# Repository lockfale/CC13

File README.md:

# CC13:
CarolinaCon13 Badge Jank

## Files:
- CC13 Badge.pdf - Detailed badge assembly guide
- ino files

## If you need to setup an Arduino build environment:

Download the latest Arduino archive from https://www.arduino.cc/en/Main/Software

Uncompress archive: xz --decompress arduino-1.8.2-linux64.tar.xz

As root untar in /usr/local and create symlink:
```
    # cd /usr/local
    # tar xvf ~/Downloads/arduino-1.8.2-linux64.tar
    # ln -s arduino-1.8.2/ arduino
```

As regular user, download badge code into home directory (--recursive will pull down dependency projects):
```
    cd
    git clone --recursive https://github.com/lockfale/CC13.git
```

## LED Patterns

To add an LED pattern:
  # In `badge/led.cpp`:
    ## Add a `const byte` array to with its own name and each sequential animation state of your desired LED pattern in binary format matching the number of LEDs in each entry.
    ## Add a branch to the `changePattern` function.
    ## Add a function for it at the bottom.
  # In `badge/led.h`:
    ## Add a function for it at the bottom.
  # In `badge/setup.cpp`:
    ## Add a submenu command for it.

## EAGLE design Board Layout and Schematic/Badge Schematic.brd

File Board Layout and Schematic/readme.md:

this is an older beta design, may not work properly but should be close.

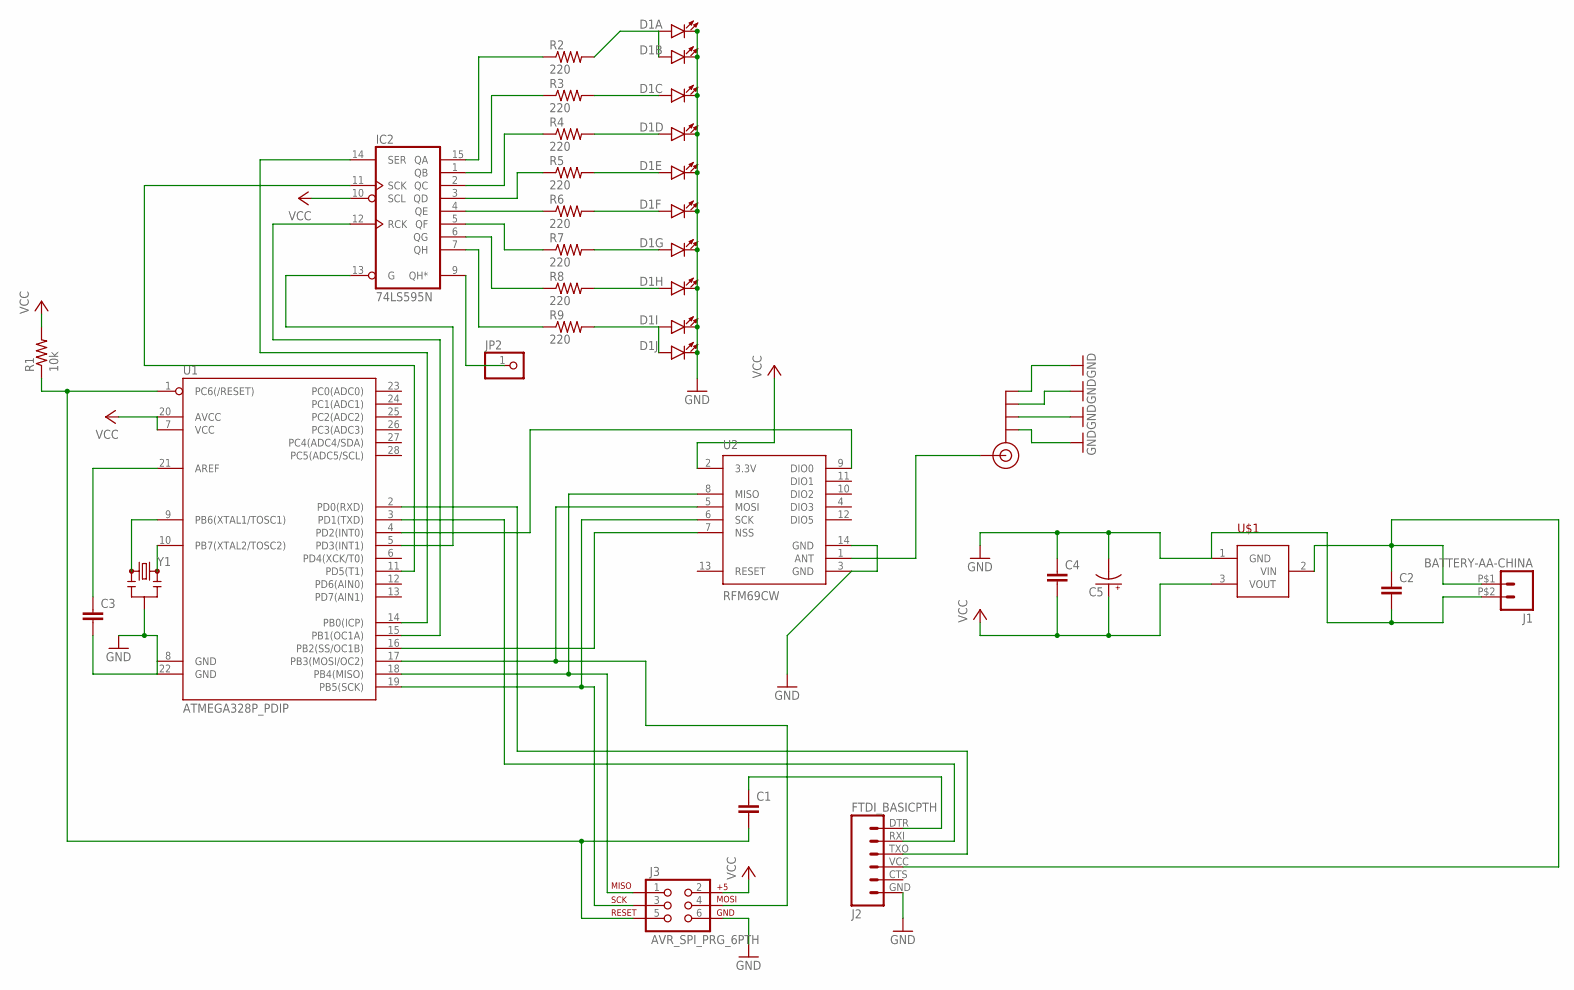
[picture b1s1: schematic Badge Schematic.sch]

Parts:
C1, C2, C3, C4: 0.1UF-50V-20%(PTH)KIT-EZ; CAP-PTH-SMALL-KIT
C5: 10UF-25V-20%(PTH)KIT; CPOL-RADIAL-10UF-25V-KIT
D1: LED_BARGRAPH_10; LED_BARGAPH_10
IC2: 74LS595N; DIL16
J1: BATTERY-AA-CHINA; BATTERY-AA-CHINA-PACKAGE
J2: FTDI_BASICPTH; FTDI_BASIC
J3: AVR_SPI_PRG_6PTH; 2X3
J$1: SMA_EDGE; SMA-EDGE
JP2: PINHD-1X1; 1X01
R1: 10k; AXIAL-0.3
R2, R3, R4, R5, R6, R7, R8, R9: 220; AXIAL-0.3EZ
U1: ATMEGA328P_PDIP; DIL28-3
U2: RFM69CW; RFM69CW-XXXS2
U$1: MCP1702-33TO92; TO-92
Y1: RESONATORPTH; RESONATOR-PTH

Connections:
GND: C2.2, C3.2, C4.1, C5.2 (-), D1.11 (C), D1.12 (C), D1.13 (C), D1.14 (C), D1.15 (C), D1.16 (C), D1.17 (C), D1.18 (C), D1.19 (C), D1.20 (C), IC2.8 (GND), J1.P$2 (2), J2.GND (6), J3.6, J$1.GND@0 (GND), J$1.GND@1 (GND), J$1.GND@2 (GND), J$1.GND@3 (GND), U1.8 (GND), U1.22 (GND), U2.3 (GND), U2.14 (GND), U$1.1 (GND), Y1.2
unnamed: J$1.SIG (SIGNAL), U2.1 (ANT)
unnamed: J3.4, U1.17 (PB3(MOSI/OC2)), U2.5 (MOSI)
unnamed: J3.1, U1.18 (PB4(MISO)), U2.8 (MISO)
unnamed: J3.3, U1.19 (PB5(SCK)), U2.6 (SCK)
unnamed: U1.4 (PD2(INT0)), U2.9 (DIO0)
unnamed: U1.16 (PB2(SS/OC1B)), U2.7 (NSS)
unnamed: IC2.13 (G), U1.5 (PD3(INT1))
unnamed: C1.1, J2.DTR (1)
unnamed: U1.10 (PB7(XTAL2/TOSC2)), Y1.3
unnamed: J2.TXO (3), U1.2 (PD0(RXD))
unnamed: J2.RXI (2), U1.3 (PD1(TXD))
unnamed: U1.9 (PB6(XTAL1/TOSC1)), Y1.1
unnamed: C2.1, J1.P$1 (1), J2.VCC (4), U$1.2 (VIN)
unnamed: IC2.7 (QH), R9.P$1 (1)
unnamed: IC2.15 (QA), R2.P$1 (1)
unnamed: IC2.6 (QG), R8.P$1 (1)
unnamed: IC2.5 (QF), R7.P$1 (1)
unnamed: C3.1, U1.21 (AREF)
unnamed: IC2.4 (QE), R6.P$1 (1)
unnamed: C1.2, J3.5, R1.P$1 (1), U1.1 (PC6(/RESET))
unnamed: IC2.3 (QD), R5.P$1 (1)
unnamed: IC2.2 (QC), R4.P$1 (1)
unnamed: IC2.1 (QB), R3.P$1 (1)
unnamed: D1.1 (A), D1.2 (A), R2.P$2 (2)
unnamed: D1.3 (A), R3.P$2 (2)
unnamed: D1.4 (A), R4.P$2 (2)
unnamed: D1.5 (A), R5.P$2 (2)
unnamed: D1.6 (A), R6.P$2 (2)
unnamed: D1.7 (A), R7.P$2 (2)
unnamed: D1.8 (A), R8.P$2 (2)
unnamed: D1.9 (A), D1.10 (A), R9.P$2 (2)
unnamed: IC2.14 (SER), U1.14 (PB0(ICP))
unnamed: IC2.12 (RCK), U1.15 (PB1(OC1A))
unnamed: IC2.11 (SCK), U1.11 (PD5(T1))
unnamed: IC2.9 (QH*), JP2.1
VCC: C4.2, C5.1 (+), IC2.10 (SCL), IC2.16 (VCC), J3.2, R1.P$2 (2), U1.7 (VCC), U1.20 (AVCC), U2.2 (3.3V), U$1.3 (VOUT)

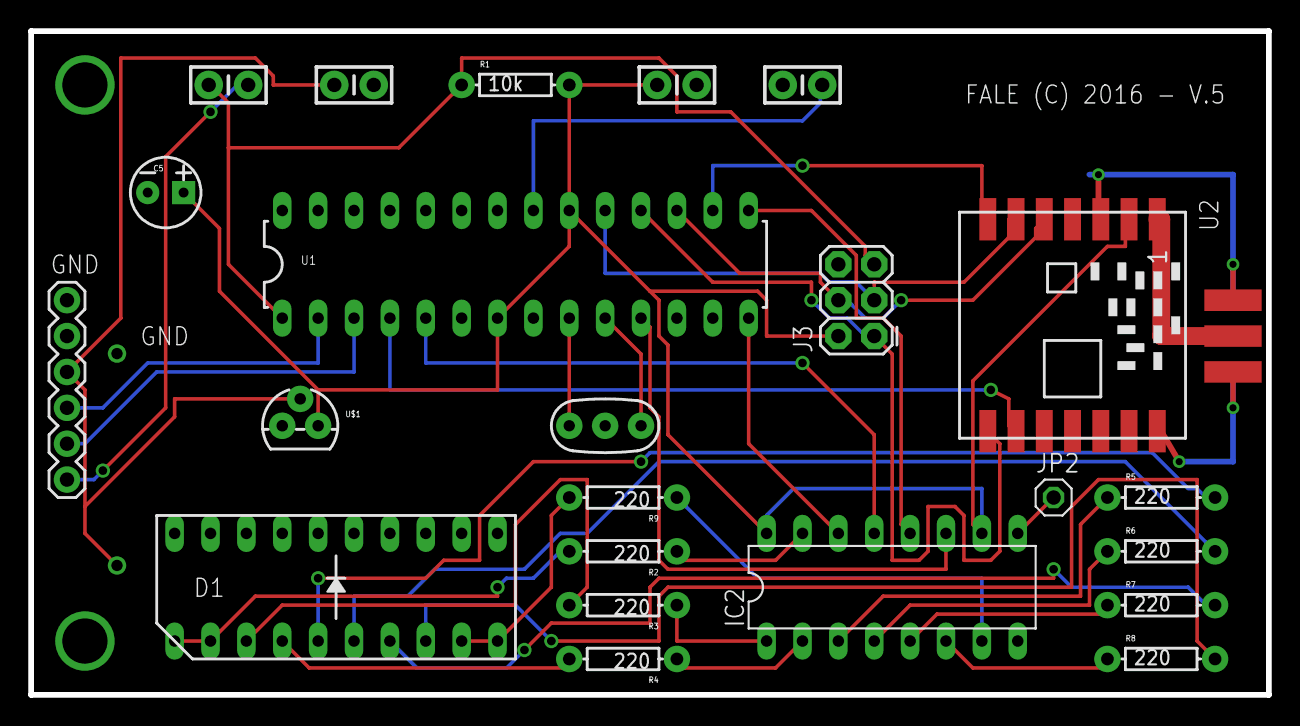
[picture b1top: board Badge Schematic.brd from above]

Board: 2 copper layers, 87.6 x 47.0 mm, 25 parts (0 on the bottom side), 37 nets.

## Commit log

2017-05-19 The needful
2017-05-19 README
2017-05-19 This is fine.
2017-05-21 Added quick new LED pattern Sparkle! Adding this to work out the process, before we get into the advanced stuff.
    Didn't unit or integration test. Let's add some unit tests later so we don't need to push the code everytime and have the badge handy?
    Added guide for adding new LED patterns to the README.
    Sorry about the whitespaces edits... For the better??
2017-05-21 Fixing all the things
2017-05-22 Fixed sparkle
2017-05-22 remove if statement in changePattern, not needed; made patterns faster
2017-05-22 Fixed Radiate2, now negradiate. For Justin
2017-05-29 adding BOM
    use this if you want to build your own.
2017-05-29 adding board schematic
    beta board schematic.

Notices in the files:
Board Layout and Schematic/Badge Schematic.brd:
FALE (C) 2016 - V.5
parts and their libraries:
SparkFun-DigitalIC: Licensing: Creative Commons ShareAlike 4.0 International - https://creativecommons.org/licenses/by-sa/4.0
